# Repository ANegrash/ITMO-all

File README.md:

# Добро пожаловать!
В этом репозитории собраны все сохранившиеся у меня работы за 4 года обучения в бакалавриате Университета ИТМО.

**Автор:** Неграш Андрей 

**Код, направление подготовки (специальность):** 09.03.01 Информатика и вычислительная техника

**Образовательная программа:** Компьютерные системы и технологии

ФПИиКТ

2019-2024

По возникающим вопросам можете обращаться по указанным на главной странице GitHub контактам, однако если здесь нет какой-то лабораторной или ответов, значит у меня этого не было или оно не сохранилось. Учебные материалы (методички, презентации и т.д.) у меня есть, сюда не выкладывал, при обращении в лс могу выслать.

Не забывайте ставить звёздочки - так я пойму, что этим кто-то пользуется и мне будет приятно;)

## Содержание

### 1 курс
- Основы профессиональной деятельности
  - [1 семестр](https://github.com/ANegrash/ITMO-all/tree/master/1%20OPD)
  - [2 семестр](https://github.com/ANegrash/ITMO-all/tree/master/2%20OPD)
- Физика
  - [1 семестр](https://github.com/ANegrash/ITMO-all/tree/master/1%20Physics)
  - [2 семестр](https://github.com/ANegrash/ITMO-all/tree/master/2%20Physics)

### 2 курс
- [Алгоритмы и структуры данных](https://github.com/ANegrash/ITMO-all/tree/master/4%20Algorithms)
- [БЖД](https://github.com/ANegrash/ITMO-all/tree/master/4%20Life%20safety)
- [Веб-программирование](https://github.com/ANegrash/ITMO-all/tree/master/3%20Web)
- [Вычислительная математика](https://github.com/ANegrash/ITMO-all/tree/master/4%20Computational%20math)
- [Языки программирования](https://github.com/ANegrash/ITMO-all/tree/master/3%20Programming%20languages)

### 3 курс
- [Архитектура компьютера](https://github.com/ANegrash/ITMO-all/tree/master/5%20Computer%20architecture)
- [Информационные системы и базы данных](https://github.com/ANegrash/ITMO-all/tree/master/5%20Information%20systems%20and%20databases)
- [Компьютерные сети](https://github.com/ANegrash/ITMO-all/tree/master/6%20Computer%20networks)
- [Операционные системы](https://github.com/ANegrash/ITMO-all/tree/master/5%20Operating%20systems)
- [Системы автоматизированного проектирования](https://github.com/ANegrash/ITMO-all/tree/master/6%20CAD%20systems)
- [Системы ввода-вывода](https://github.com/ANegrash/ITMO-all/tree/master/6%20IO%20systems)
- [Системы искусственного интеллекта](https://github.com/ANegrash/ITMO-all/tree/master/5%20Artificial%20intelligence%20systems)
- [Тестирование программного обеспечения](https://github.com/ANegrash/ITMO-all/tree/master/6%20Software%20testing)
- [Функциональная схемотехника](https://github.com/ANegrash/ITMO-all/tree/master/6%20Functional%20circuitry)

### 4 курс
- [Защита и действия человека в условиях ЧС](https://github.com/ANegrash/ITMO-all/tree/master/8%20Protection%20and%20actions%20in%20emergency%20situations)
- [Метрология, стандартизация и сертификация](https://github.com/ANegrash/ITMO-all/tree/master/7%20Metrology)
- [Моделирование](https://github.com/ANegrash/ITMO-all/tree/master/7%20Modeling)
- [Практика](https://github.com/ANegrash/ITMO-all/tree/master/8%20Practice)
- [Проектирование вычислительных систем](https://github.com/ANegrash/ITMO-all/tree/master/7%20Computer%20systems%20design)
- [Проектная документация](https://github.com/ANegrash/ITMO-all/tree/master/8%20Project%20documentation)
- [Системы на кристалле](https://github.com/ANegrash/ITMO-all/tree/master/7%20Systems%20on%20a%20chip)
- [Теория надёжности](https://github.com/ANegrash/ITMO-all/tree/master/7%20Reliability%20theory)
- [Технологии нейросетевых вычислений](https://github.com/ANegrash/ITMO-all/tree/master/7%20Neural%20network%20computing%20technologies)

## Полезные ссылки 
Здесь указаны ссылки на репозитории моих сокурсников или студентов предыдущих лет, которыми я активно пользовался во время обучения.

- https://github.com/testpassword?tab=repositories
- https://github.com/buffer404/university
- https://github.com/EgorMIt/ITMO/
- https://github.com/Avvessalom?tab=repositories
- https://github.com/RedGry/ITMO
- https://github.com/band-of-four/cheatsheets

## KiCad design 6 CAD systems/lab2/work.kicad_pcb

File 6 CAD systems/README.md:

# Системы автоматизированного проектирования
**Автор:** Неграш Андрей

**Преподаватель:** Поляков Владимир Иванович

Университет ИТМО, 2023

## Лабораторная 1

**Вариант:** 19

Отчёт доступен в папке [lab1](https://github.com/ANegrash/ITMO-all/tree/master/6%20CAD%20systems/lab1)

## Лабораторная 2

Все файлы доступны в папке [lab2](https://github.com/ANegrash/ITMO-all/tree/master/6%20CAD%20systems/lab2)

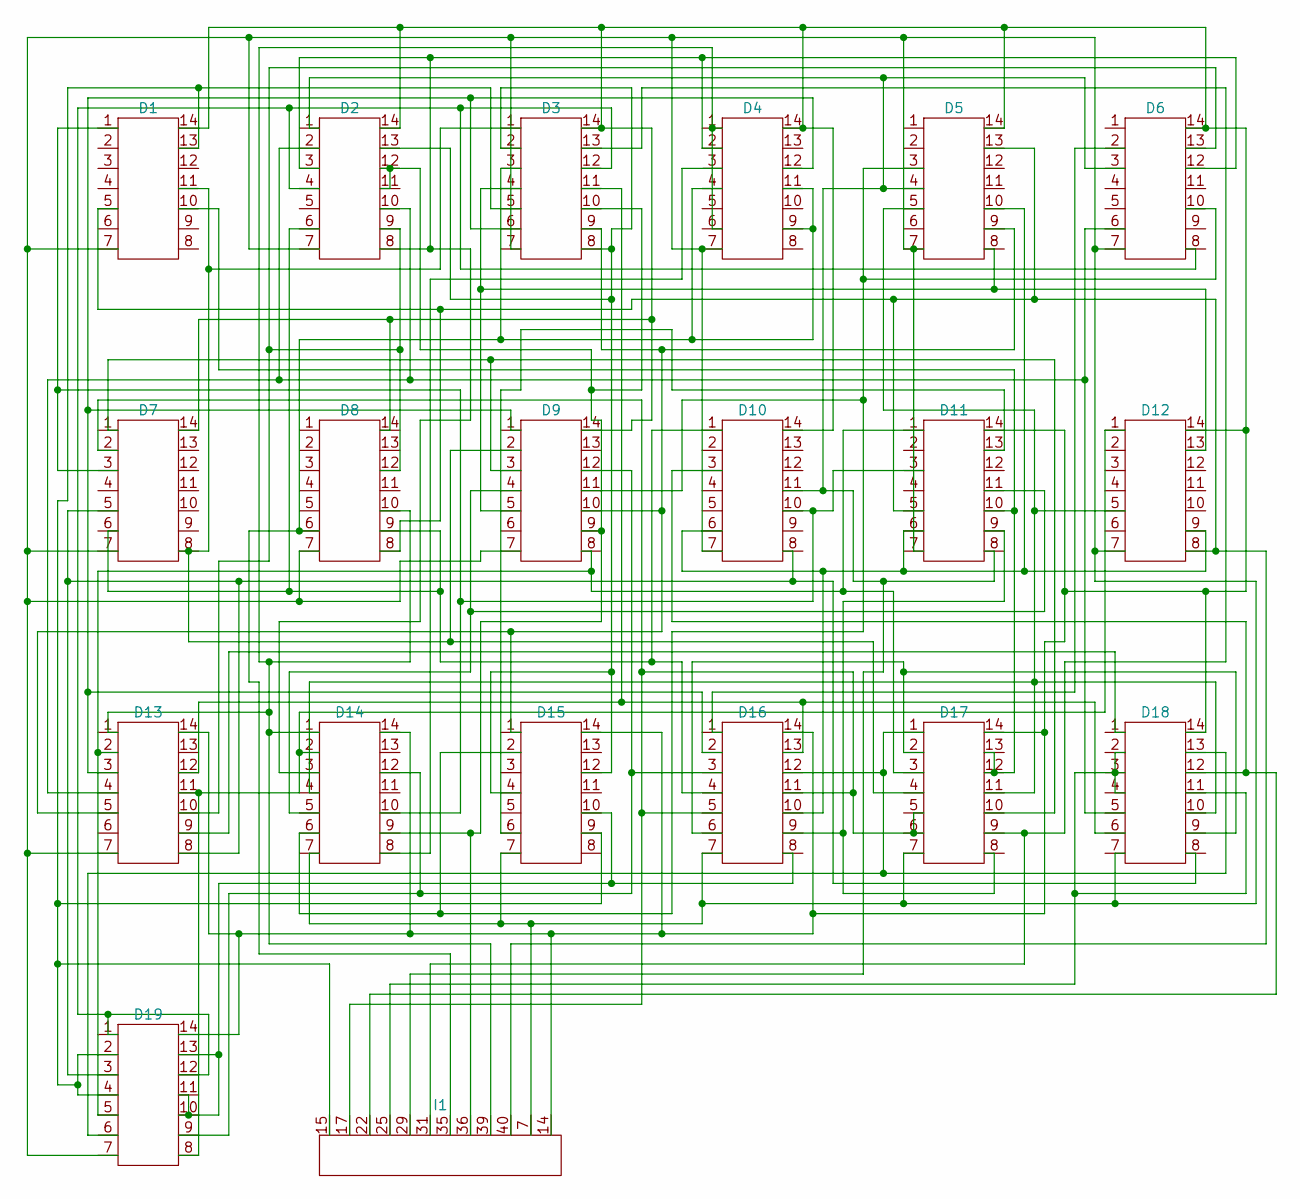
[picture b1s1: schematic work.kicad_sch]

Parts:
D1, D2, D3, D4, D5, D6, D7, D8, D9, D10, D11, D12, D13, D14, D15, D16, D17, D18, D19: MYCONN
I1: INP

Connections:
unnamed: D1.1, D7.3, D10.10, D11.3, D14.10
unnamed: D1.5, D5.13, D8.8, D11.5, D12.8, I1.40
unnamed: D1.7, D2.7, D3.7, D4.7, D5.7, D6.7, D7.7, D8.7, D9.7, D10.7, D11.7, D12.7, D13.7, D14.7, D15.7, D16.7, D17.7, D18.7, D19.7, I1.7
unnamed: D1.10, D11.10, D17.12, D17.13
unnamed: D1.11, D3.1, D7.8, D9.2, D17.4
unnamed: D1.13, D3.5, D15.9, D19.2, D19.4, I1.15
unnamed: D1.14, D2.14, D3.14, D4.14, D5.14, D6.14, D7.14, D8.14, D9.14, D10.14, D11.14, D12.14, D13.14, D14.14, D15.14, D16.14, D17.14, D18.14, D19.14, I1.14
unnamed: D3.3, D4.4, D4.9, D4.11, D8.6, I1.35
unnamed: D2.6, D7.6, D8.9, D10.1, D16.4
unnamed: D10.3, D18.12, I1.22
unnamed: D5.10, D10.6, D11.6, D12.9, D16.10
unnamed: D7.5, D10.8, D13.8, D18.8, D19.3
unnamed: D2.1, D5.4, D6.3, D10.11, D11.8, I1.29
unnamed: D9.8, D11.1, D13.2, D17.3, D19.5
unnamed: D11.9, D16.9, D17.8
unnamed: D9.4, D11.11, D14.5
unnamed: D11.13, D15.6
unnamed: D12.1, D13.11, D14.2, D19.8
unnamed: D5.5, D12.5, D14.4, D17.11, D18.10
unnamed: D3.4, D5.8, D9.5, D12.13
unnamed: D4.1, D4.6, D8.10, D13.1, D14.1, I1.39
unnamed: D3.6, D4.12, D9.1, D13.3, D16.2
unnamed: D2.2, D2.10, D6.6, D13.4, D18.5
unnamed: D3.9, D5.9, D9.10, D13.5, D15.1
unnamed: D13.9, D18.1
unnamed: D2.9, D6.13, D8.12, D13.10
unnamed: D3.11, D13.12, D16.13, D18.6
unnamed: D2.3, D2.8, D4.2, D6.12, D14.3
unnamed: D5.3, D6.10, D9.11, D14.6, D15.2
unnamed: D4.3, D14.8
unnamed: D2.11, D2.12, D3.10, D9.9, D14.9, I1.36
unnamed: D9.12, D14.12, D16.3, D19.9
unnamed: D15.10, D16.8, D19.10, D19.11, D19.13
unnamed: D2.13, D3.2, D3.8, D15.4, D15.12
unnamed: D6.2, D16.1
unnamed: D16.6, D17.2, D18.9
unnamed: D7.2, D16.5, D16.11, D17.5, D17.6, I1.17
unnamed: D16.12, D17.1, D18.13, D19.6
unnamed: D3.13, D17.9, I1.31
unnamed: D7.1, D9.3, D17.10
unnamed: D18.2, D18.3, D18.4, D18.11, I1.25
unnamed: D2.4, D3.12, D6.8, D19.1, D19.12

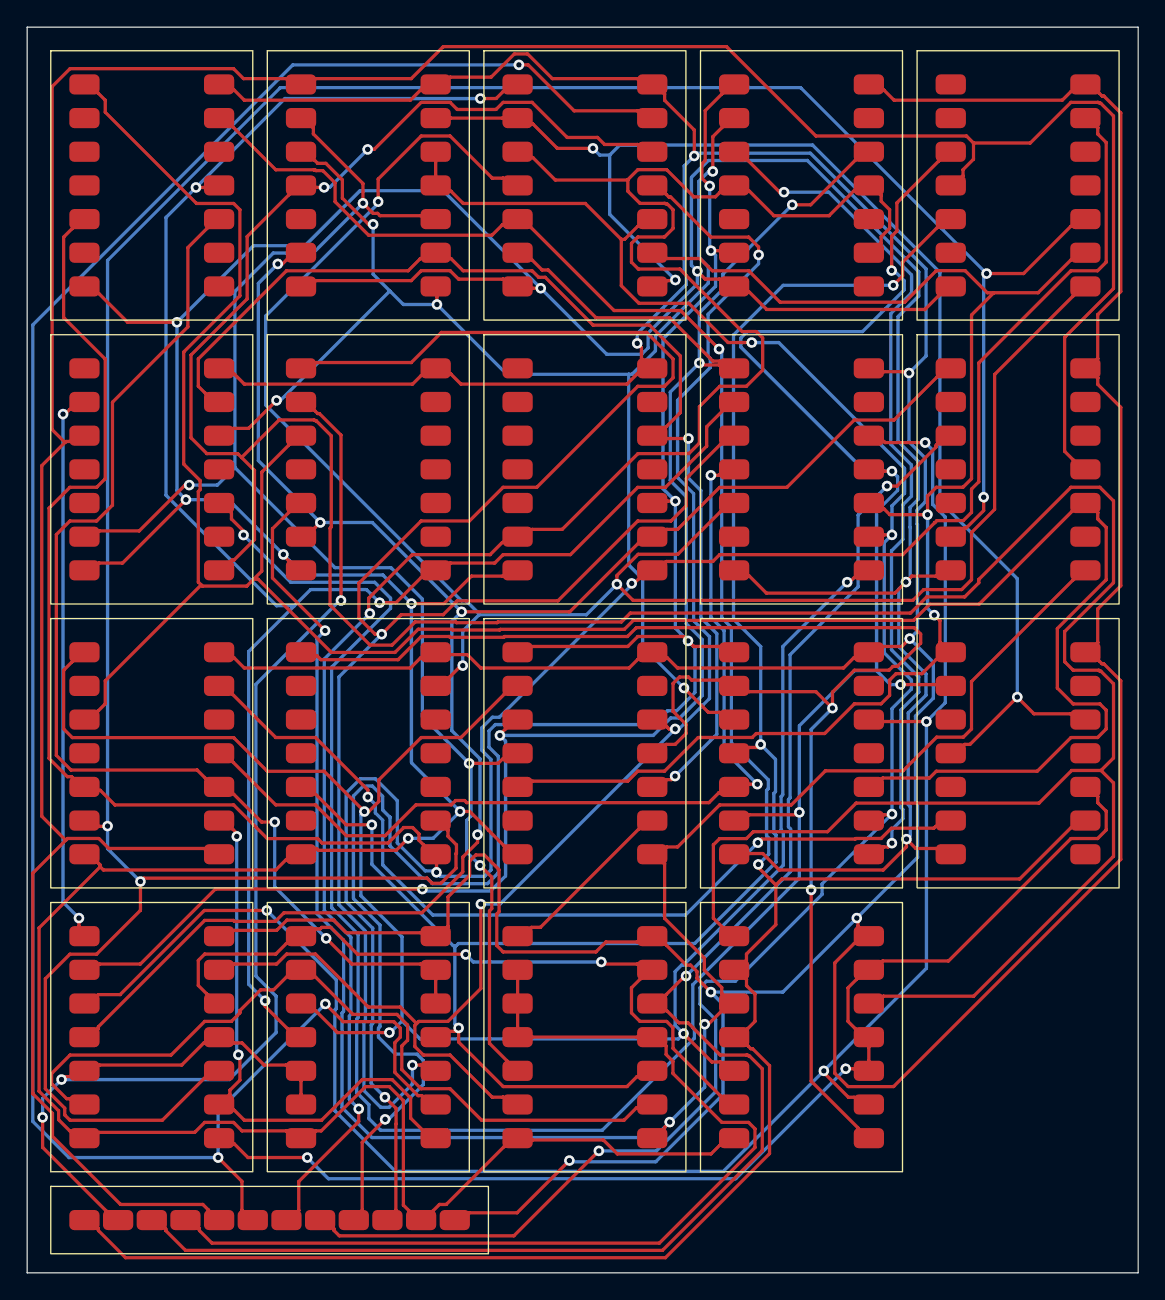
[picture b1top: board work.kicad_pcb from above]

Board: 2 copper layers, 83.8 x 94.0 mm, 20 parts (0 on the bottom side), 42 nets.

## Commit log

2023-11-22 Основы профессиональной деятельности
2023-11-22 Физика
2023-11-22 web lab1 files
2023-11-22 web lab1 report
2023-11-22 web lab1 readme
2023-11-22 web lab2 files
2023-11-22 web lab2 readme
2023-11-22 web lab3 readme
2023-11-22 web lab3 files
2023-11-22 Веб-программирование
2023-11-22 pl lab1
2023-11-22 pl lab2
2023-11-22 pl lab3
2023-11-22 pl lab4
2023-11-22 Языки программирования
2023-11-22 Введение в алгоритмы
2023-11-22 Сортировка
2023-11-22 Структуры данных
2023-11-22 Алгоритмы на графах
2023-11-22 Алгоритмы и структуры данных
2023-11-22 Безопасность жизнедеятельности
2023-11-22 comp-math lab1
2023-11-22 Вычислительная математика
2023-11-22 isdb things
2023-11-22 Информационные системы и базы данных
2023-11-22 ai labs
2023-11-22 Системы искусственного интеллекта
2023-11-22 Архитектура компьютера
2023-11-22 comp netw labs
2023-11-22 Компьютерные сети
2023-11-22 cad labs
2023-11-22 Системы автоматизированного проектирования
2023-11-22 io labs
2023-11-22 Системы ввода/вывода
2023-11-22 func_circ labs
2023-11-22 Функциональная схемотехника
2023-11-22 Тестирование программного обеспечения
2023-11-22 reliability theory labs
2023-11-22 Теория надёжности
2023-11-22 Метрология, стандартизация и сертификация
2023-11-22 Моделирование
2023-11-22 Проектирование вычислительных систем
2023-11-23 Технологии нейросетевых вычислений
2023-12-15 Добро пожаловать!
2023-12-18 Операционные системы
2023-12-25 Системы на кристалле
2024-01-23 Главная
2024-03-24 Проектная документация
2024-03-24 Защита и действия человека в условиях ЧС
2024-03-24 Практика
2024-03-25 Главная страница
